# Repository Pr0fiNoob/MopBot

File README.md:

# MopBot

MopBot ist ein experimenteller Bodenreinigungsroboter. Die Python-Software **MopSlothOS** läuft auf einem Raspberry Pi und übernimmt Navigation sowie die übergeordnete Steuerung. Über eine serielle Schnittstelle kommuniziert sie mit einem Arduino, dessen Firmware die Hardware ansteuert.

> **Projektstatus:** Frühphase. Das Repository enthält derzeit nur erste Grundlagen; Software, Firmware und die Elektronik werden schrittweise ergänzt.

## Ziele

- Den Roboter mit einer klaren Zustandsmaschine steuern.
- Eine zuverlässige und dokumentierte serielle Kommunikation zwischen Raspberry Pi und Arduino entwickeln.
- Eine sichere Grundlage für Antrieb, Sensoren und Reinigungsfunktion schaffen.
- Eine einfache Flächennavigation entwickeln, zunächst mit einem Schlangenlinienmuster.

## Konzept

Der Raspberry Pi trifft die übergeordneten Entscheidungen, etwa zur Navigation und zum aktuellen Betriebszustand. Er übermittelt passende Befehle an den Arduino. Die Arduino-Firmware steuert anschliessend die angebundene Hardware wie Motoren, Sensoren oder weitere Aktoren.

## Geplante Repository-Struktur

Die folgende Struktur beschreibt den Zielaufbau des Repositories. Bis alle Teile umgesetzt sind, können einzelne Ordner oder Dateien noch fehlen.

```text
MopBot/
├── .gitignore
├── LICENSE
├── README.md
├── AGENTS.md
├── CONTRIBUTING.md
├── python/
│
├── PCBs/
│   ├── Motor_Shield_v1/
│   │   └── ... KiCad-Projektdateien
│   └── ... weitere KiCad-Projekte
└── arduino-firmware/
    └── MopBot-firmware/
        └── MopBot-firmware.ino

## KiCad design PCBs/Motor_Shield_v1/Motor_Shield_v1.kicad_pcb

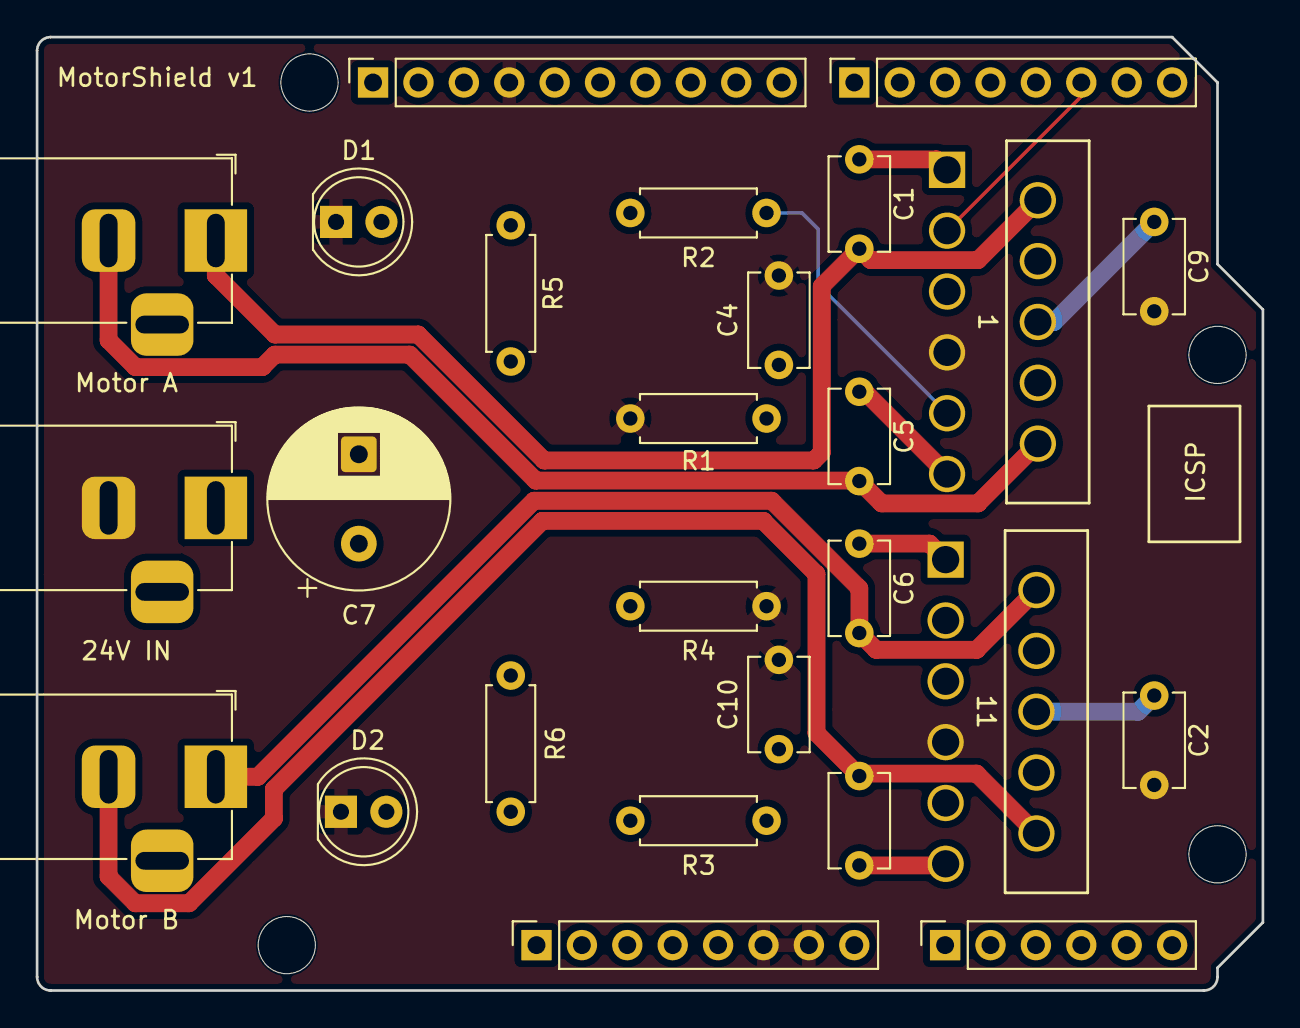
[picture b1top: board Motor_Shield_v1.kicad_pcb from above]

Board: 4 copper layers, 68.6 x 53.3 mm, 30 parts (0 on the bottom side), 27 nets.

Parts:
1, 11: LMD18200T
24V IN: Barrel_Jack; BarrelJack_Horizontal
C1, C5, C6, C8: 10nF; C_Disc_D5.1mm_W3.2mm_P5.00mm
C2, C9: 1µF; C_Disc_D5.1mm_W3.2mm_P5.00mm
C4, C10: 100nF; C_Disc_D5.1mm_W3.2mm_P5.00mm
C7: 680µF; CP_Radial_D10.0mm_P5.00mm
D1, D2: TEMP_WARN; LED_D5.0mm
J1: Power; PinSocket_1x08_P2.54mm_Vertical
J2: Digital/PWM; PinSocket_1x10_P2.54mm_Vertical
J3: Analog; PinSocket_1x06_P2.54mm_Vertical
J4: Digital/PWM; PinSocket_1x08_P2.54mm_Vertical
MH1, MH2, MH3, MH4: MountingHole_3.2mm
Motor A: Barrel_Jack; BarrelJack_Horizontal
Motor B: Barrel_Jack; BarrelJack_Horizontal
R1, R4: 1.8kΩ; R_Axial_DIN0207_L6.3mm_D2.5mm_P7.62mm_Horizontal
R2, R3: 10kΩ; R_Axial_DIN0207_L6.3mm_D2.5mm_P7.62mm_Horizontal
R5, R6: 220Ω; R_Axial_DIN0207_L6.3mm_D2.5mm_P7.62mm_Horizontal

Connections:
+5V: J1.5, R2.1, R3.1
+24V: 1.6 (VS), 11.6 (VS), 24V IN.1, C2.1, C7.1, C9.1
/2: 1.3 (DIR), J4.6
/4: 1.4 (BRAKE), J4.4
/7: 1.9 (THERM), J4.1, R2.2
/8: 11.3 (DIR), J2.10
/12: 11.4 (BRAKE), J2.6
/*3: 1.5 (PWM), J4.5
/*5: 11.5 (PWM), J4.3
/*6: 11.9 (THERM), J4.2, R3.2
/*9: J2.9, R6.2
/*10: J2.8, R5.2
/A2: 11.8 (I_SEN), C10.1, J3.3, R4.1
/A3: 1.8 (I_SEN), C4.1, J3.4, R1.1
/SCL/A5: J2.1, J3.6
/SDA/A4: J2.2, J3.5
GND: 1.7 (GND), 11.7 (GND), 24V IN.2, C2.2, C4.2, C7.2, C9.2, C10.2, D1.1 (K), D2.1 (K), J1.6, J1.7, J2.4, R1.2, R4.2
unnamed: 1.1 (BS_1), C1.1
unnamed: 1.11 (BS_2), C5.1
unnamed: 1.2 (OUT_1), C1.2, Motor A.1
unnamed: 1.10 (OUT_2), C5.2, Motor A.2
unnamed: 11.1 (BS_1), C6.2
unnamed: 11.11 (BS_2), C8.2
unnamed: 11.2 (OUT_1), C6.1, Motor B.1
unnamed: 11.10 (OUT_2), C8.1, Motor B.2
unnamed: D1.2 (A), R5.1
unnamed: D2.2 (A), R6.1
